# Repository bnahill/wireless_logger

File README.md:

Wireless Logger
===============

A compact wireless inertial logging and processing hardware platform. This may include multiple designs of different names. Software may also be included soon.

Licensing
=========

Hardware designs in this package are licensed under the TAPR Open Hardware License v1.0.

Software presented here is licensed under the GNU General Public License version 3 (GPLv3).

The terms of both licenses are included in this repository. If you would like to use these works in another projects which would otherwise violate the terms of their respective licenses, please contact me and perhaps we can work something out. While I support both the free hardware/software movements, I understand that such licenses may excessively constrain groups with otherwise noble causes.

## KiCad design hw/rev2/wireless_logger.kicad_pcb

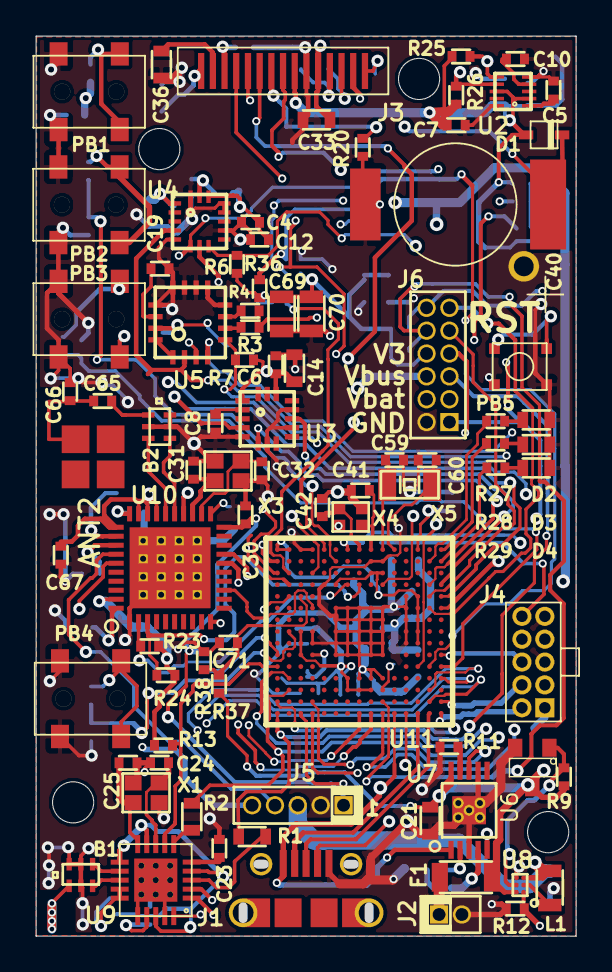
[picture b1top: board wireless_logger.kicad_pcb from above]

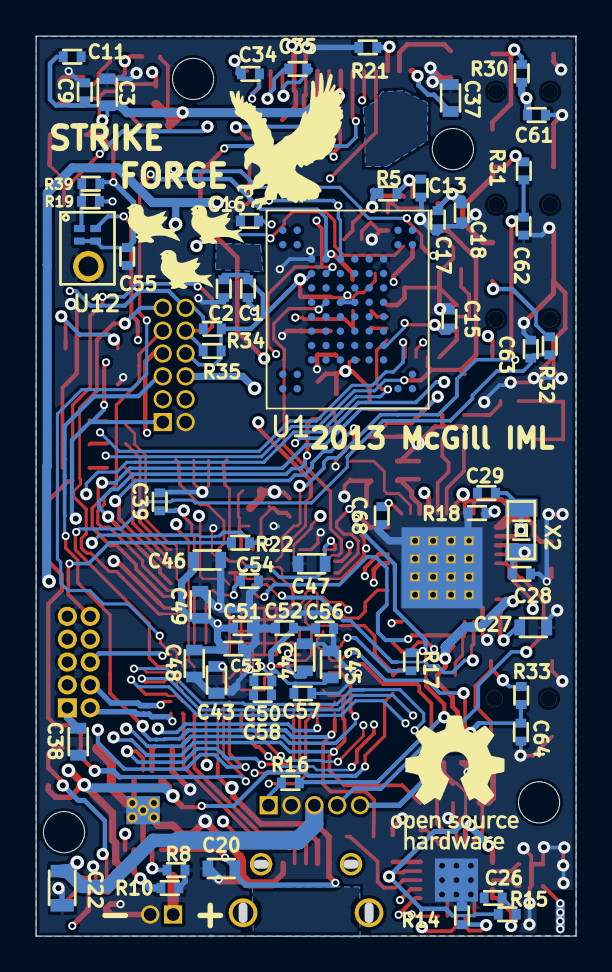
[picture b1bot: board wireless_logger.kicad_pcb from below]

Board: 4 copper layers, 30.0 x 50.0 mm, 155 parts (66 on the bottom side), 112 nets.

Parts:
ANT2: Molex 47948; MOLEX_47948
B1: 0915BM15A0001; JOHAN_BALUN_FILT
B2: 2450BM15A0002; JOHAN_BALUN_FILT
C1, C55: 0.1u; SMD0402
C2, C7, C18, C34, C35, C67, C68, C71: 1u; SMD0402
C3, C14, C20, C21, C33, C36, C37, C38, C43, C44, C45, C46, C47, C48, C49: 2.2u; SMD0603
C4, C5, C8, C9, C10, C11, C12, C15, C17, C23, C50, C51, C52, C53, C61, C62, C63, C64: 100n; SMD0402
C6, C16: 100p; SMD0402
C13, C19, C26, C39, C54, C56, C57, C58: 10n; SMD0402
C22, C69, C70: 10u; SMD0805
C24, C25, C41, C42: 5p; SMD0402
C27: 1u; SMD0603
C28, C29: 15p; SMD0402
C30: 1n; SMD0402
C31, C32: 12p; SMD0402
C40: DSK-3R3H224U-HL; DSK-XXXXXX-HL
C59, C60: 9p; SMD0402
C65, C66: CAP; SMD0402
D1: BAT43XV2; SOD-523F
D2: LS Q976-NR-1; SMD0603
D3: LW Q38G-Q1S1-3K6L-1; SMD0603
D4: LB Q39E-N1P1-35-1; SMD0603
F1: PTS120616V025; SMD1206
J1: FCI 10118194; FCI_10118194
J2: CONN_2; HDR_2X1_50MIL
J3: SSD1306_SER; LY091WG15
J4: SWD_10PIN; SULLINS_5X2_050_THRU
J5: CONN_5; HDR_5X1_50MIL
J6: CONN_6X2; HDR_6X2_50MIL
L1: MLP2016S1R0M; SMD0805
PAD_0_5x1_5: VAL**; PAD_0_5x1_5
PB1, PB2, PB3, PB4: EVQPSD
PB5: KMT0
R1, R2: 100k; SMD0603
R3, R4: 4.7k; SMD0402
R5: 4.7R; SMD0402
R6, R7, R13: 220k; SMD0402
R8: 1k; SMD0402
R9: 680k; SMD0402
R10: 2k; SMD0402
R11, R12: 470k; SMD0402
R14, R18: 56k (1%); SMD0402
R15: 4R7; SMD0402
R16: 2.7k; SMD0402
R17: 22k; SMD0402
R19: 0R; SMD0402
R20, R36: 100k; SMD0402
R21: 390k; SMD0402
R22, R23, R24, R25, R26, R34, R35: 10k; SMD0402
R27, R28, R29: RES; SMD0402
R30, R31, R32, R33: 3.3k; SMD0402
R37, R38, R39: 1M; SMD0402
SCREW_HOLE_2-56, SCREW_HOLE_2-56#2, SCREW_HOLE_2-56#3, SCREW_HOLE_2-56#4: VAL**; SCREW_HOLE_2-56
U1: MT29FXX01A; MICRON_VFBGA63
U2: MAG3110
U3: MMA8452Q; MMA8451Q
U4: LPS331AP
U5: L3GD20
U6: MCP111T-315; SOT23
U7: BQ24095; BQ24095_MSOP
U8: TPS62698
U9: CC1101
U10: CC2541
U11: STM32F40X_BGA176; STM32F4_BGA176
U12: MEMS_DGTL_MIC; ADMP521
VAL: MCGILL
VAL#2: EAGLE
VAL#3: OSHW
X1: FA-128 26.0000MF10Z-W3; FA-128
X2, X5: 9HT10-32.768KBZF-T; TXC_9HT10
X3: FA-128 32.0000MF20X-K3; FA-128
X4: XRCGB25M000F0L00R0; XRCGB_F_N

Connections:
/Bluetooth/BT_ANT_DN: B2.3, U10.26
/Bluetooth/BT_ANT_DP: B2.4, U10.25
/Bluetooth/BT_ANT_SE: ANT2.1, C65.2, C66.1
/Bluetooth/RF_DC: J5.4, U10.34
/Bluetooth/RF_DD: J5.5, U10.35
/Bluetooth/RF_RESET_N_LOCAL: C30.2, R16.1, R17.1, U10.20
/Bluetooth/RX_MISO: U10.17, U11.H15
/Bluetooth/TX_MOSI: U10.16, U11.G15
/Guardian Interface/GDO0: R2.1, U9.6
/Guardian Interface/GDO2: R1.1, U9.3
/OLED/SCLK: J3.11, U1.K6, U11.P4
/OLED/SDIN: J3.12, U1.J7, U11.R3
/Power/MODE: R12.2, U8.A1, U11.N15
/STM32F4/BT_NRESET: R17.2, U11.R10
/STM32F4/CC1101_nCS: R13.2, U9.7, U11.R11
/STM32F4/EXTI1: R3.1, R4.1, U11.M3
/STM32F4/EXTI2: U10.13, U11.M6
/STM32F4/EXTI5: C61.2, R30.2, U11.P5
/STM32F4/EXTI6: C62.2, R31.2, U11.K2
/STM32F4/EXTI7: C63.2, R32.2, U11.A11
/STM32F4/EXTI8: C64.2, R33.2, U11.P8
/STM32F4/FLASH_nCS: R36.1, U1.K7, U11.B11
/STM32F4/GYRO_nCS: R7.1, U5.5, U11.A6
/STM32F4/I2C2_SCL: R24.2, U10.3, U11.H4
/STM32F4/I2C2_SDA: R23.2, U10.2, U11.J4
/STM32F4/I2C3_SCL: J6.12, R34.2, U11.F15
/STM32F4/I2C3_SDA: J6.10, R35.2, U11.F14
/STM32F4/LED1: R27.2, U11.B2
/STM32F4/LED2: R28.2, U11.A1
/STM32F4/LED3: R29.2, U11.A2
/STM32F4/OLED_nCS: J3.8, U11.L1
/STM32F4/OLED_nD/C: J3.10, U11.R2
/STM32F4/OLED_nRES: J3.9, R20.2, U11.F4
/STM32F4/REG_nCHG: U7.8, U11.M14
/STM32F4/REG_nUSB_CONN: U7.5, U11.M15
/STM32F4/SPI1_MISO: U1.G7, U11.P3
/STM32F4/SPI2_CLK: J6.1, R2.2, R19.1, U11.P13
/STM32F4/SPI2_MISO: J6.3, U11.R14, U12.DAT
/STM32F4/SPI2_MOSI: J6.5, R1.2, U11.R15
/STM32F4/SPI2_NSS: J6.7, U11.P12
/STM32F4/SWCLK: J4.4, U11.A14
/STM32F4/SWDIO: J4.2, U11.A15
/STM32F4/SWO: J4.6, U11.A10
/STM32F4/USART1_RX: J6.9, U11.B5
/STM32F4/USART1_TX: J6.11, U11.B6
/STM32F4/USB_D+: J1.3, U11.B15
/STM32F4/USB_D-: J1.2, U11.C15
/STM32F4/USB_ID: J1.4, U11.D15
/Sensors/ACC_I2C_SCL: R26.2, U2.7, U3.4, U11.A5
/Sensors/ACC_I2C_SDA: R25.2, U2.6, U3.6, U11.B4
/Sensors/ACC_INT1: U3.11, U11.A4
/Sensors/GYR_DRDY_INT2: R3.2, U5.6
/Sensors/GYR_INT1: R4.2, U5.7
/Sensors/GYR_SPI_CLK: U4.4, U5.2, U9.1, U11.B14
/Sensors/GYR_SPI_MISO: U4.7, U5.4, U9.2, U11.B13
/Sensors/GYR_SPI_MOSI: U4.6, U5.3, U9.20, U11.A12
/Sensors/PRS_SPI_nCS: R6.1, U4.8, U11.C11
GND: B1.2, B1.5, B1.6, B2.2, B2.5, B2.6, C1.1, C2.1, C3.1, C4.1, C5.1, C6.1, C7.1, C8.1, C9.1, C10.1, C11.1, C12.1, C13.1, C14.1, C15.1, C16.1, C17.1, C18.1, C19.2, C20.1, C21.1, C22.1, C23.1, C24.1, C25.1, C26.1, C27.1, C28.2, C29.2, C30.1, C31.2, C32.2, C33.1, C36.1, C37.1, C38.1, C39.1, C40.2, C41.2, C42.2, C43.1, C44.1, C45.1, C46.1, C47.1, C48.1, C49.1, C50.1, C51.1, C52.1, C53.1, C54.1, C55.1, C56.1, C57.1, C58.1, C59.2, C60.2, C61.1, C62.1, C63.1, C64.1, C66.2, C67.1, C68.1, C69.1, C70.1, C71.1, D2.2, D3.2, D4.2, J1.5, J2.2, J3.6, J4.3, J4.5, J4.9, J5.2, J6.2, PB1.2, PB2.2, PB3.2, PB4.2, PB5.2, R8.1, R10.1, R11.1, R12.1, R14.1, R18.2, R20.1, R21.1, R38.1, U1.K3, U1.K8, U2.5, U2.10, U3.5, U3.7, U3.10, U3.12, U4.5, U4.10, U4.12, U4.13, U4.16, U5.8, U5.9, U5.10, U5.11, U5.12, U5.13, U6.2, U7.3, U7.7, U7.GND, U8.C2, U9.16, U9.19, U9.GND, U10.1, U10.GND, U11.D5, U11.D6, U11.D7, U11.D8, U11.D9, U11.F2, U11.F6, U11.F7, U11.F8, U11.F9, U11.F10, U11.F12, U11.G2, U11.G6, U11.G7, U11.G8, U11.G9, U11.G10, U11.G12, U11.H6, U11.H7, U11.H8, U11.H9, U11.H10, U11.H12, U11.J6, U11.J7, U11.J8, U11.J9, U11.J10, U11.K6, U11.K7, U11.K8, U11.K9, U11.K10, U11.L4, U11.M1, U11.M8, U11.M9, U11.N1, U12.GND, X1.GND, X3.GND, X4.GND
unnamed: PB2.1, R31.1
unnamed: PB4.1, R33.1
unnamed: PB3.1, R32.1
unnamed: PB1.1, R30.1
unnamed: R19.2, R39.2, U12.CLK
unnamed: C60.1, U11.E1, X5.1
unnamed: C39.2, C40.1, D1.2, U11.C1
unnamed: C43.2, U11.F13
unnamed: C44.2, U11.M10
unnamed: J4.10, R22.2
unnamed: C42.1, U11.H1, X4.2
unnamed: C41.1, U11.G1, X4.1
unnamed: C71.2, R37.1, R38.2, U11.N5
unnamed: C59.1, U11.F1, X5.2
unnamed: D2.1, R27.1
unnamed: D4.1, R29.1
unnamed: D3.1, R28.1
unnamed: PB5.1, R22.1, U11.J1
unnamed: C13.2, R5.2, U4.15
unnamed: C5.2, U2.1
unnamed: C10.2, U2.4
unnamed: C8.2, U3.2
unnamed: C19.1, U5.14
unnamed: R8.2, U7.2
unnamed: R11.2, U7.9
unnamed: R10.2, U7.4
unnamed: L1.1, U8.B1
unnamed: F1.1, J2.1
unnamed: R9.1, U6.1, U8.B2
unnamed: R14.2, U9.17
unnamed: C24.2, U9.8, X1.1
unnamed: C25.2, U9.10, X1.2
unnamed: C26.2, R15.1, U9.14, U9.15
unnamed: B1.3, U9.13
unnamed: B1.4, U9.12
unnamed: C23.2, U9.5
unnamed: R18.1, U10.30
unnamed: C27.2, U10.40
unnamed: C29.1, U10.32, X2.2
unnamed: B2.1, C65.1
unnamed: C28.1, U10.33, X2.1
unnamed: J5.1, R16.2
unnamed: C32.1, U10.22, X3.1
unnamed: C31.1, U10.23, X3.2
unnamed: C37.2, J3.15
unnamed: C36.2, J3.14
unnamed: J3.13, R21.2
unnamed: C34.2, J3.2
unnamed: C34.1, J3.1
unnamed: C35.1, J3.3
unnamed: C35.2, J3.4
V3: C1.2, C2.2, C3.2, C4.2, C6.2, C7.2, C9.2, C11.2, C12.2, C14.2, C15.2, C16.2, C17.2, C18.2, C22.2, C38.2, C45.2, C46.2, C47.2, C48.2, C49.2, C50.2, C51.2, C52.2, C53.2, C54.2, C55.2, C56.2, C57.2, C58.2, C67.2, C68.2, C69.2, C70.2, D1.1, J3.7, J4.1, J5.3, J6.8, L1.2, R5.1, R6.2, R7.2, R13.1, R15.2, R23.1, R24.1, R25.1, R26.1, R34.1, R35.1, R36.2, R39.1, U1.D3, U1.G5, U1.G6, U1.J8, U2.2, U2.8, U3.1, U3.14, U4.1, U4.14, U5.1, U5.15, U5.16, U8.C1, U9.4, U9.9, U9.11, U9.18, U10.10, U10.21, U10.24, U10.27, U10.28, U10.29, U10.31, U10.39, U11.C5, U11.C6, U11.C7, U11.C8, U11.C9, U11.F3, U11.G3, U11.G13, U11.H13, U11.J12, U11.J13, U11.K4, U11.N8, U11.N9, U11.N10, U11.P1, U11.R1, U12.LR, U12.VDD
Vbat: C21.2, C33.2, F1.2, J3.5, J6.4, R9.2, R37.2, U6.3, U7.10, U8.A2
Vbus: C20.2, J1.1, J6.6, U7.1, U11.E15

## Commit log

2013-05-10 Started rev2 of logger with bigger MCU and better power management
2013-05-16 Schematic nearly final, placement beginning
2013-05-29 Uhhhh, secondary interconnect assignment and a LOT of routing
2013-05-29 Optimized some routes and passes DRC. Still need to do RF traces
2013-05-31 Ready for first schematic review
2013-06-01 Route and placement optimization. Added holes. Reduced number of ports used
2013-06-01 Updated BQ24095 to MSOP package (free samples) and verified connections
2013-06-01 Fixed huge problem with regulator footprint pin layout
2013-06-01 Added pullup to flash nCS
2013-06-01 Added some extra decoupling caps for bluetooth
2013-06-01 Minor rerouting stuffs
2013-06-02 STM32 checked -- Some optimization done on routes and important filtering bits
2013-06-02 Fixed misconnected CC1101 debug output to SPI2
2013-06-02 Added regulator datasheet
2013-06-02 Added more datasheets
2013-06-03 Added licenses
2013-06-03 Moved silks around!
2013-06-03 Rev 2a submitted to OSH Park for manufacture
2013-06-04 Set soldermask clearance to zero
2013-06-24 Changed P1 to J6. This was changed for the silks on rev2a but not back-annotated
2013-07-10 Updated PCB to 5 mil trace/space for more-reasonably-sized BGA pads
2013-07-11 Added isolation for flash power and battery voltage monitoring
2013-07-12 Finished more small connections
2013-07-12 Added super-slick graphics and standardized silk print sizes
2013-07-14 Moved to NSMD BGA mounting and moved silks around.
2013-07-16 Hardware rev2b submitted for manufacturing. Minor touchups.
2013-08-20 Restructured files a little
2013-08-20 Initial commit of files that should build for both GCC and Keil
2013-08-20 A few things: Added L3GD20 gyroscope and corresponding SPI drivers. Added Platform namespace for all platform-specific configuration stuff Added a bunch more documentation for various things Added im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
2013-08-20 Added new ChibiOS-based project
2013-08-20 Added MAG3110 driver
2013-08-20 More advanced EXTI control, added support for LSM303 interrupts (not working)
2013-08-20 Added more fonts and made a common interface to all sensor readings
2013-08-20 Added more documentation for MAG3110
2013-08-20 A lot of things... FANCY new SPI drivers OLED driver Framebuffer Font library
2013-08-20 Flip screen
2013-08-20 Better division of win32 and unix toolchain parameters
2013-08-20 Fixed toolchain config: Now works with CMake 2.8.10 which would still prefer native toolchain
2013-08-20 Added Doxygen configuration and added a lot of documentation
2013-08-20 Added progress bar
2013-08-20 Enabled (and fixed) more compiler warnings
2013-08-20 Made CMake build in Windows with MinGW
2013-08-20 Made start.gdb copying work for windows too
2013-08-20 This works with the instructions provided for Windows build
2013-08-20 Added fancy GUI with menus
2013-08-20 Added CMSIS DSP, took ChibiOS out of static library due to compile issues
2013-08-20 Added an acquisition event source for sensor results
2013-08-20 Made it possible to adjust output rate of accelerometer
2013-08-20 Added parametrized wrapper class and platform configuration for USB CDC
2013-08-20 Added documentation for LTC3559
2013-08-20 Broke project into smaller library components
2013-08-20 Forgot to add two files
2013-08-20 Moved RTC functions where they belong
2013-08-20 Added CMSIS includes that I forgot
2013-08-20 Started basic PySide GUI
2013-08-20 Modified the USB terminal interface to be less human-friendly and more machine-friendly. Machines are better than people.
2013-08-20 Added USB transfer screen
2013-08-20 Fixed linker flag to prevent discarding of some important regions
2013-08-20 Added A lot of graphics to the GUI and separated out some of the USBScreen functionality to a class not necessarily associated with the OLED GUI
2013-08-20 Added suspend timeout for UI/display
2013-08-20 Added RTC code and command to set the clock over USB Ready to merge to main
2013-08-20 Added basic CC1101 code
2013-08-20 Removed USB terminal cmd_settime_ts
2013-08-20 More early developments in wireless
2013-08-20 Reorganized exernal interrupts in a non-interruptcentric way Also make CC1101 initialize correctly
2013-08-20 Updated logger GUI to support new USB protocol
2013-08-20 Updated USB protocol to be slightly more robst and a bunch of other related items
2013-08-20 Added basic Guardian driver to control CC1101
2013-08-20 Added basic clock speed switching
2013-08-20 Added files I forgot
2013-08-20 Yet another commit with A LOT of stuff in it. Unfortunately, there are a lot of interdependencies which I don't want to break down so I'm making this all one commit. I'm the only one working on this,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
2013-08-20 Nothing significant. Just need to move to other 'puter
2013-08-20 Got rid of YAFFS
2013-08-20 Added a little bit of documentation and moved to some more explicit namespacing for Platform
2013-08-20 Fixed up both CC1101 and Guardian drivers to initialize properly
2013-08-20 Started (but haven't tested) flash module
2013-08-20 The filesystem; it works!
2013-08-20 Started fixing problems with the filesystem not really being flash-friendly
2013-08-20 Added Coffee FS and some minimal Contiki components Added a few new UI items including a basic test suite Got flash driver working too
2013-08-20 Improved command inspection -- next up, better parsing with pyparsing
2013-08-20 Added event logging capabilities, connected alternate CC1101
2013-08-20 Added flash ECC test
2013-08-20 Started adding streaming options to USB interface
2013-08-20 Remote command inspection nearly complete -- need buffering/streaming commands
2013-08-20 Made buttons use some fancy debouncing
2013-08-20 Replaces vector inversion with optimized assembly
2013-08-20 Logger GUI command parser is more robust using pyparsing
2013-08-20 Added untested support for queueing of sensor data
2013-08-20 Added a fancy and efficient print function
2013-08-20 Missed a file
2013-08-20 Improved PC UI to handle arbitrary buffers and specialized command handlers
2013-08-20 Forgot a file
2013-08-20 Updated documentation formatting
2013-08-20 Fixed the sensor queuing!
2013-08-20 Updated datasource structures to actually move data...
2013-08-20 Started basic integration with FlogFS
2013-08-20 Got rid of pesky readme
2013-08-20 Fixed stupid bug in event log menu where it would crash sometimes
2013-08-20 FORGOT TO ADD A FILE
2013-08-20 Fix to flash continued read and lots of USB interface improvements
2013-08-20 Handle string buffers better
2013-08-20 Support for new-style USB iface arrays and fancy buffer types
2013-08-20 Added compile option to not use FPU
2013-08-20 Fixed multi-sector writes. Screw you Micron. Your documentation is crap.
2013-08-20 Changed to 4-byte USB commands on logger side
2013-08-20 Fixed array parser -- (remote 'ls' now works)
2013-08-20 Change command length to a 4-byte integer on GUI side
2013-08-20 Updated to CMSIS 3.20
2013-08-20 Got rid of excessive printing when recieving large buffers
2013-08-20 Added OpenOCD RTOS support automatically when not using FPU
2013-08-20 Added fs_rm command to USB terminal
2013-08-20 Added large file FLogFS test
2013-08-20 USB terminal changed heavily to allow for more efficient buffering: Now command matching happens immediately after the command string; Commands themselves now handle parameters on both the PC and emb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
2013-08-20 Forgot to add flogfs_conf_implement.h
2013-08-20 Made UI completely static, added sensor logging test, allowed timeout in UI wait_for_button
2013-08-20 Added scheduler tick frequency option
2013-08-20 Added some super-slick clock and sensor management stuff: Scheduler runs fine of RTC Switches to HSI/HSE as needed by applications Automatically enable and disable each sensor as required
2013-08-20 Added options for ChibiOS debugging, also fixed accelerometer acquisition
2013-08-20 Updated datasource to safely allow peek, added reference counting to acquisition, sped up OLED clock
2013-08-20 Moved board-dependent platform stuff around
2013-08-20 Re-enabled 32k crystal (was broken on FS test unit)
2013-08-20 Platform init mounts flash
2013-08-20 Added CMake configuration options for important things like clock management and SVD files
2013-08-20 FLogFS testing complete
2013-08-20 Added FLogFS submodule
2013-08-20 Added SF configuration, got rid of pins that I don't use on mt29x
2013-08-20 Now disable flash too
2013-08-20 Fixed options
2013-08-20 Changed acquisition API, flash now supports opening write-only
2013-08-20 Fixed up accelerometer driver to be templated for different variants
2013-08-20 Stop flashing the LED on clock changes...
2013-08-21 Fixed SF board configuration for GPIOB/I2C1
2013-09-12 MADE SPI RUN IN APPLICATION THREADS FOR BETTER RESPONSIVENESS Patched up UI for SF
2013-09-21 Initialize button states correctly...
2013-09-21 Fixed MMA845x scaling for 12/14-bit devices
2013-09-21 Fixed I2C peripherals on SF
2013-09-21 More explicit SPI initialization in flash module
2013-09-24 Prepared upgrade to hw rev2c: Changes: Larger pads on flash BGA for easier mounting Move a few signals that were close to sensitive clock connections Remap more things to SPI1, USART1, and USART6 to 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
2013-09-27 Submitted rev2c for manufacturing
2013-09-29 Tiny update to bottom silk screen. This acutally made it into the manufacturing of rev2c by email
2013-11-27 Updated to hw rev2c pin and peripheral mapping Also got rid of semaphore synchronization for MMA845x, should do others Also added more documentation to acquisition framework
2013-11-27 Add some hardware assembly instructions
2013-11-27 Fixed incorrect SPI assignment for gyro also insufficent stack size for acquisition threads
2013-11-27 Added more assembly notes regarding crystal orientation debacle
2013-11-27 Added assembly note about TPS62698
2013-11-27 Corrected formatting on assembly instructions
2013-12-02 Upgraded ChibiOS to 2.6.1 to fix some HAL bugs kicking around So far, the only problem is a hardfault in FlogFS mounting now That will be dealt with later, in a session dedicated to fixing FlogFS
2013-12-05 Updating to patched FlogFS
2013-12-05 Added safety against multiple initializations in MT29xx
2013-12-05 Added 'back' button support in UI
2013-12-08 Holy crap -- a lot, but it's all intertwined and so is lumped together -Datasources now name the types required for more-easily defined listeners -Fractional types introduced; hopefully let sensors u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
2013-12-08 Updated to flogfs with a stupid fix
2013-12-24 Fixed FLogFS and flash initialization failure Both areas followed a messed up sequence upon failure due to incorrect error checking.
2013-12-24 Fixed suspend not being reenabled after sensorview
2013-12-24 Don't use clock manager before initialized...
2014-09-04 Fixed dependency for GDB targets that shouldn't be there
2014-09-04 Workaround for RTC union and internal compier error w/ GCC 4.9
2014-09-04 Re-incorporated mixed-precision code from AudioPulse
